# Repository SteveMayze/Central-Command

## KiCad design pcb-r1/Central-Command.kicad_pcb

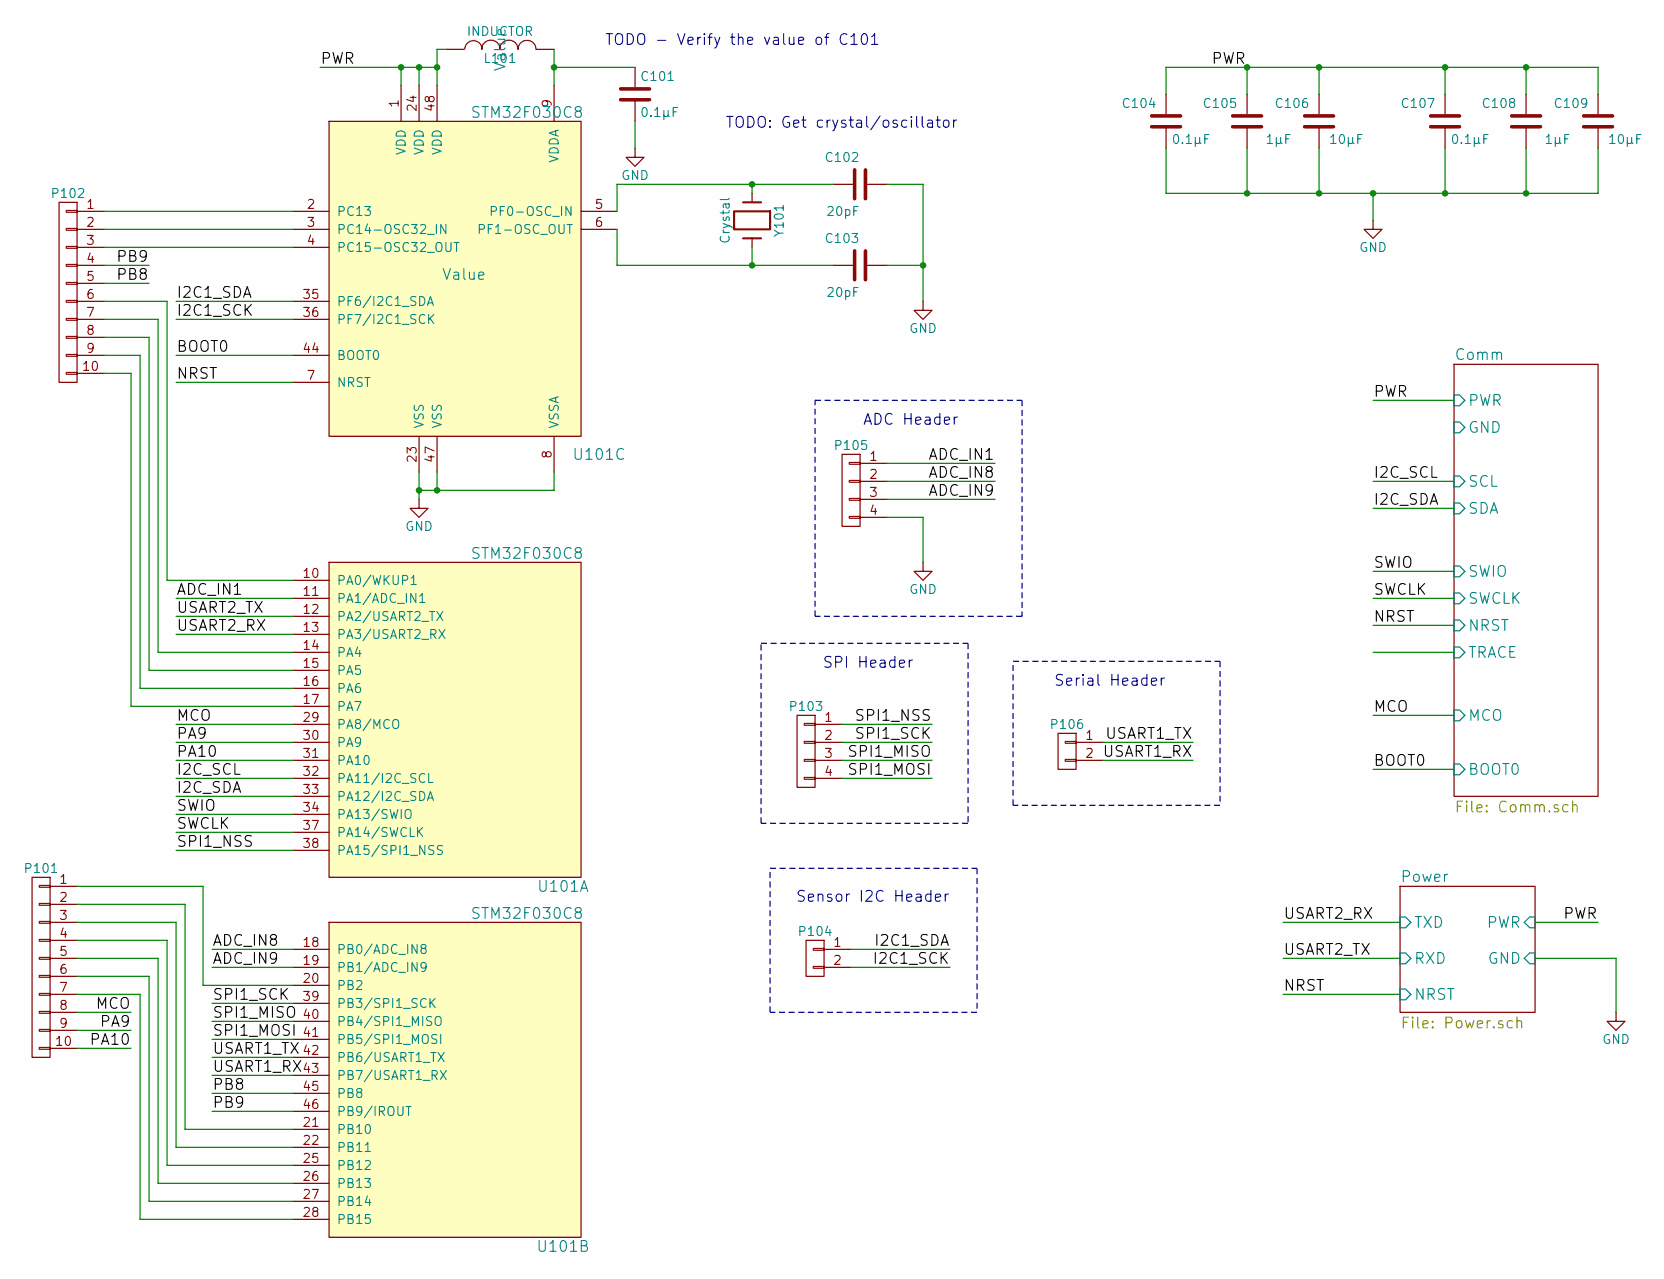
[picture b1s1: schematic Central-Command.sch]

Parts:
C101, C104, C107: 0.1μF; C_0805; DigiKeyPN 478-1395-1-ND
C102, C103: 20pF; C_0805; DigiKeyPN 1276-1829-1-ND
C105, C108: 1μF; C_1206; DigiKeyPN 311-1951-1-ND
C106, C109: 10μF; C_1206; DigiKeyPN 1276-2865-1-ND
L101: INDUCTOR; Neosid_Inductor_SM1206; MPN LQH31CN100K03L; DigiKeyPN 490-6588-1-ND
P101, P102: CONN_01X10; Pin_Header_Straight_1x10
P103, P105: CONN_01X04; Pin_Header_Straight_1x04
P104, P106: CONN_01X02; Pin_Header_Straight_1x02
U101: STM32F030C8; LQFP-48_7x7mm_Pitch0.5mm
Y101: Crystal; Crystal_HC49-U_Vertical; MPN FOXSLF/080-20; DigiKeyPN 631-1100-ND

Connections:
/ADC_IN1: P105.1, U101.11 (PA1/ADC_IN1)
/ADC_IN8: P105.2, U101.18 (PB0/ADC_IN8)
/ADC_IN9: P105.3, U101.19 (PB1/ADC_IN9)
/Comm/BOOT0: U101.44 (BOOT0); also elsewhere on the board
/Comm/NRST: U101.7 (NRST); also elsewhere on the board
/Comm/PWR: C104.2, C105.2, C106.2, C107.2, C108.2, C109.2, L101.1, U101.1 (VDD), U101.24 (VDD), U101.48 (VDD); also elsewhere on the board
/Comm/SCL: U101.32 (PA11/I2C_SCL); also elsewhere on the board
/Comm/SDA: U101.33 (PA12/I2C_SDA); also elsewhere on the board
/Comm/SWCLK: U101.37 (PA14/SWCLK); also elsewhere on the board
/Comm/SWIO: U101.34 (PA13/SWIO); also elsewhere on the board
/I2C1_SCK: P104.2, U101.36 (PF7/I2C1_SCK)
/I2C1_SDA: P104.1, U101.35 (PF6/I2C1_SDA)
/MCO: P101.8, U101.29 (PA8/MCO)
/PA9: P101.9, U101.30 (PA9)
/PA10: P101.10, U101.31 (PA10)
/PB8: P102.5, U101.45 (PB8)
/PB9: P102.4, U101.46 (PB9/IROUT)
/Power/RXD: U101.12 (PA2/USART2_TX); also elsewhere on the board
/Power/TXD: U101.13 (PA3/USART2_RX); also elsewhere on the board
/SPI1_MISO: P103.3, U101.40 (PB4/SPI1_MISO)
/SPI1_MOSI: P103.4, U101.41 (PB5/SPI1_MOSI)
/SPI1_NSS: P103.1, U101.38 (PA15/SPI1_NSS)
/SPI1_SCK: P103.2, U101.39 (PB3/SPI1_SCK)
/USART1_RX: P106.2, U101.43 (PB7/USART1_RX)
/USART1_TX: P106.1, U101.42 (PB6/USART1_TX)
GND: C101.2, C102.2, C103.2, C104.1, C105.1, C106.1, C107.1, C108.1, C109.1, P105.4, U101.8 (VSSA), U101.23 (VSS), U101.47 (VSS); also elsewhere on the board
unnamed: C101.1, L101.2, U101.9 (VDDA)
unnamed: C102.1, U101.5 (PF0-OSC_IN), Y101.1
unnamed: C103.1, U101.6 (PF1-OSC_OUT), Y101.2
unnamed: P101.1, U101.20 (PB2)
unnamed: P101.2, U101.21 (PB10)
unnamed: P101.3, U101.22 (PB11)
unnamed: P101.4, U101.25 (PB12)
unnamed: P101.5, U101.26 (PB13)
unnamed: P101.6, U101.27 (PB14)
unnamed: P101.7, U101.28 (PB15)
unnamed: P102.1, U101.2 (PC13)
unnamed: P102.2, U101.3 (PC14-OSC32_IN)
unnamed: P102.3, U101.4 (PC15-OSC32_OUT)
unnamed: P102.6, U101.10 (PA0/WKUP1)
unnamed: P102.7, U101.14 (PA4)
unnamed: P102.8, U101.15 (PA5)
unnamed: P102.9, U101.16 (PA6)
unnamed: P102.10, U101.17 (PA7)

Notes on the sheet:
TODO: Get crystal/oscillator
ADC Header
SPI Header
Serial Header
Sensor I2C Header
TODO - Verify the value of C101

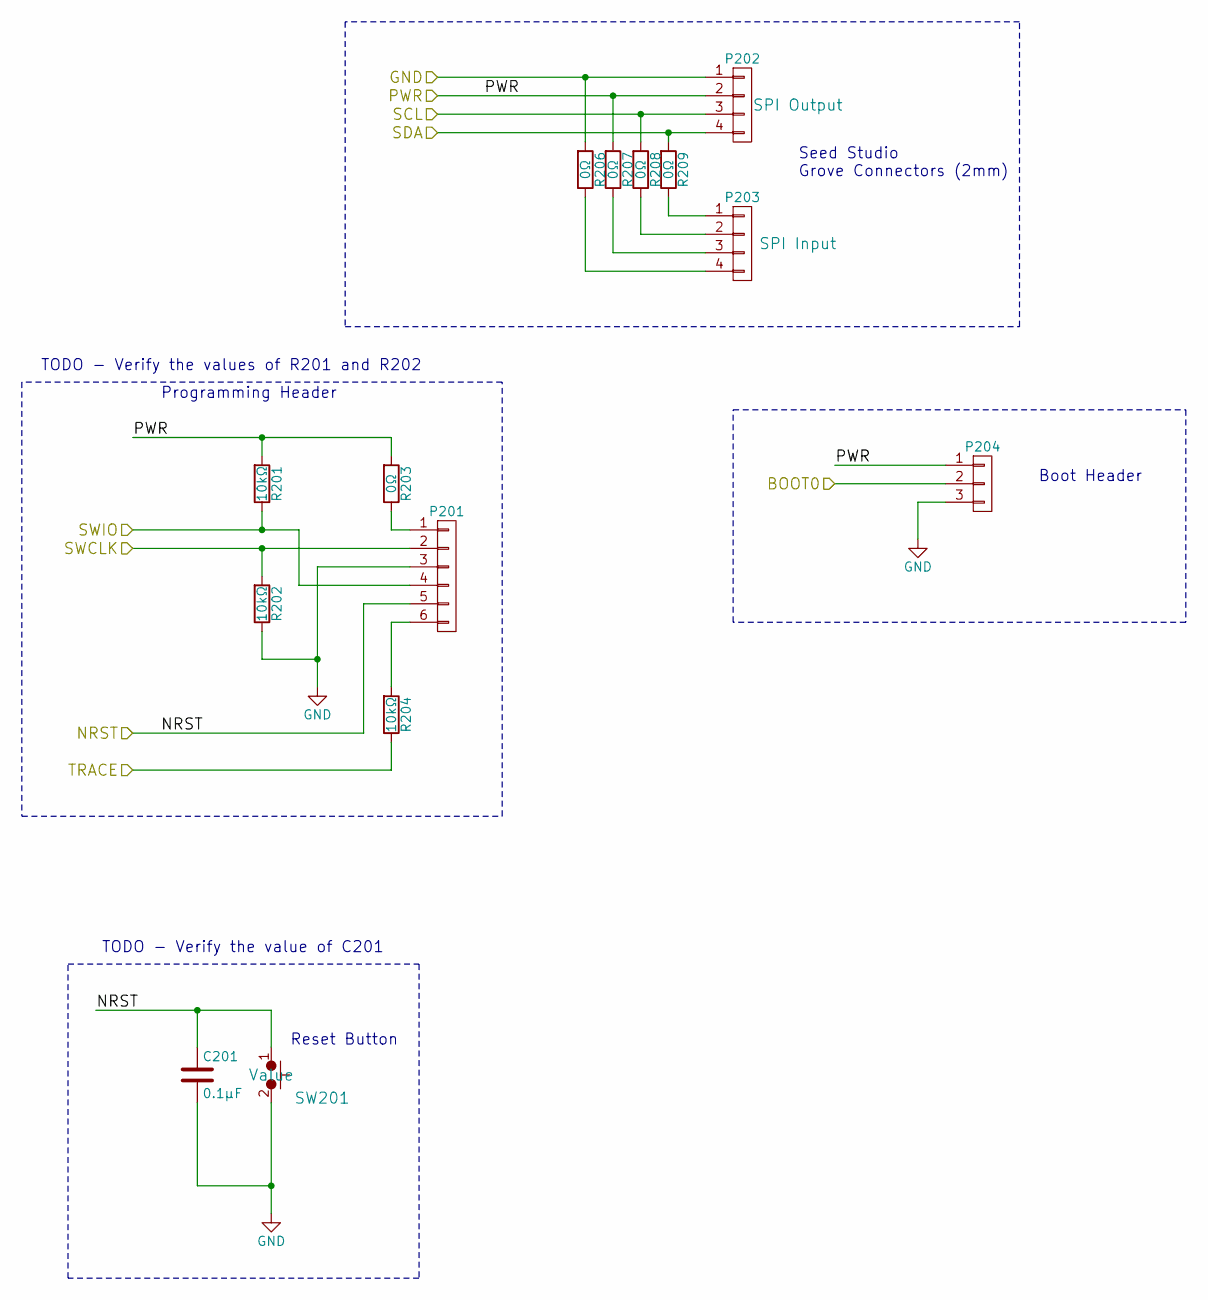
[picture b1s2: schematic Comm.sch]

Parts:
C201: 0.1μF; C_0805; DigiKeyPN 478-1395-1-ND
P201: CONN_01X06; Pin_Header_Straight_1x06; DigiKeyPN 952-2247-ND
P202, P203: CONN_01X04; Grove-2mm; MPN Value
P204: CONN_01X03; Pin_Header_Straight_1x03
R201, R202, R204: 10kΩ; R_0805; DigiKeyPN 311-10.0KCRCT-ND
R203, R206, R207, R208, R209: 0Ω; R_0805
SW201: TL3315NF160Q; PTS525SM15SMTR2LFS; MPN FSM2JSMAA; DigiKeyPN FSM2JSMAA-ND

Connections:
/Comm/BOOT0: P204.2; also elsewhere on the board
/Comm/NRST: C201.1, P201.5, SW201.1; also elsewhere on the board
/Comm/PWR: P202.2, P204.1, R201.2, R203.2, R207.2; also elsewhere on the board
/Comm/SCL: P202.3, R208.2; also elsewhere on the board
/Comm/SDA: P202.4, R209.2; also elsewhere on the board
/Comm/SWCLK: P201.2, R202.2; also elsewhere on the board
/Comm/SWIO: P201.4, R201.1; also elsewhere on the board
/Comm/TRACE: R204.1
GND: C201.2, P201.3, P202.1, P204.3, R202.1, R206.2, SW201.2; also elsewhere on the board
unnamed: P201.1, R203.1
unnamed: P201.6, R204.2
unnamed: P203.1, R209.1
unnamed: P203.2, R208.1
unnamed: P203.3, R207.1
unnamed: P203.4, R206.1

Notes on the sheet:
Reset Button
Programming Header
Seed Studio Grove Connectors (2mm)
Boot Header
TODO - Verify the values of R201 and R202
TODO - Verify the value of C201

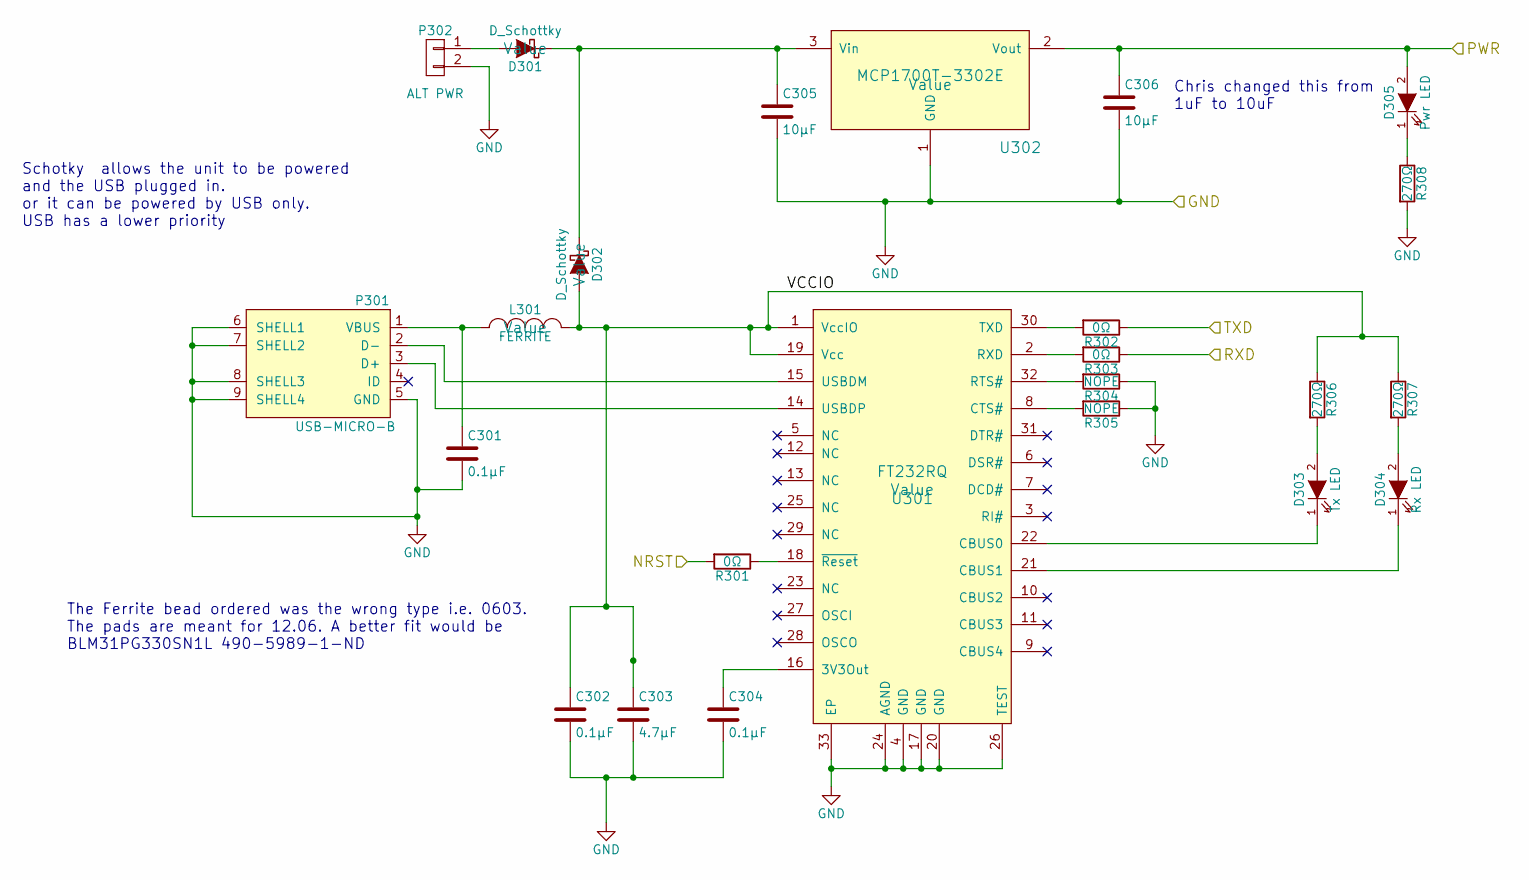
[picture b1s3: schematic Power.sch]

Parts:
C301: 0.1μF; C_0805
C302, C304: 0.1μF; C_0805; DigiKeyPN 478-1395-1-ND
C303: 4.7μF; C_0805; DigiKeyPN 1276-1856-1-ND
C305: 10μF; C_1210; DigiKeyPN 1276-2865-1-ND
C306: 10μF; C_1210
D301, D302: D_Schottky; SMA_Standard; MPN B130-13-F; DigiKeyPN B130-FDICT-ND
D303: Tx LED; LED-0805
D304: Rx LED; LED-0805
D305: Pwr LED; LED-0805; Voltage Value; DigiKeyPN Value
L301: FERRITE; Neosid_Inductor_SM1206; Voltage Value; MPN BLM31PG330SN1L; DigiKeyPN 490-5989-1-ND
P301: USB-MICRO-B; USB_Micro_B
P302: ALT PWR; Pin_Header_Straight_1x02
R301, R302, R303: 0Ω; R_0805
R304, R305: NOPE; R_0805
R306, R307, R308: 270Ω; R_0805
U301: FT232RQ; QFN-32-1EP_5x5mm_Pitch0.5mm; MPN FT232RQ-REEL; DigiKeyPN 768-1008-1-ND
U302: MCP1700T-3302E; SOT-23; MPN MCP1700T-3302E/TT; DigiKeyPN MCP1700T3302ETTCT-ND

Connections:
/Comm/NRST: R301.2; also elsewhere on the board
/Comm/PWR: C306.1, D305.2 (A), U302.2 (Vout); also elsewhere on the board
/Power/RXD: R303.1; also elsewhere on the board
/Power/TXD: R302.1; also elsewhere on the board
/Power/VCCIO: C302.1, C303.1, D302.2 (A), L301.2, R306.1, R307.1, U301.1 (VccIO), U301.19 (Vcc)
GND: C301.2, C302.2, C303.2, C304.2, C305.2, C306.2, P301.5 (GND), P301.6 (SHELL1), P301.7 (SHELL2), P301.8 (SHELL3), P301.9 (SHELL4), P302.2, R304.1, R305.1, R308.2, U301.4 (GND), U301.17 (GND), U301.20 (GND), U301.24 (AGND), U301.26 (TEST), U301.33 (EP), U302.1 (GND); also elsewhere on the board
unnamed: C301.1, L301.1, P301.1 (VBUS)
unnamed: C304.1, U301.16 (3V3Out)
unnamed: C305.1, D301.1 (K), D302.1 (K), U302.3 (Vin)
unnamed: D301.2 (A), P302.1
unnamed: D303.1 (K), U301.22 (CBUS0)
unnamed: D303.2 (A), R306.2
unnamed: D304.1 (K), U301.21 (CBUS1)
unnamed: D304.2 (A), R307.2
unnamed: D305.1 (K), R308.1
unnamed: P301.2 (D-), U301.15 (USBDM)
unnamed: P301.3 (D+), U301.14 (USBDP)
unnamed: R301.1, U301.18 (~Reset)
unnamed: R302.2, U301.30 (TXD)
unnamed: R303.2, U301.2 (RXD)
unnamed: R304.2, U301.32 (RTS#)
unnamed: R305.2, U301.8 (CTS#)

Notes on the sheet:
Schotky allows the unit to be powered and the USB plugged in. or it can be powered by USB only. USB has a lower priority
Chris changed this from 1uF to 10uF
The Ferrite bead ordered was the wrong type i.e. 0603. The pads are meant for 12.06. A better fit would be BLM31PG330SN1L 490-5989-1-ND

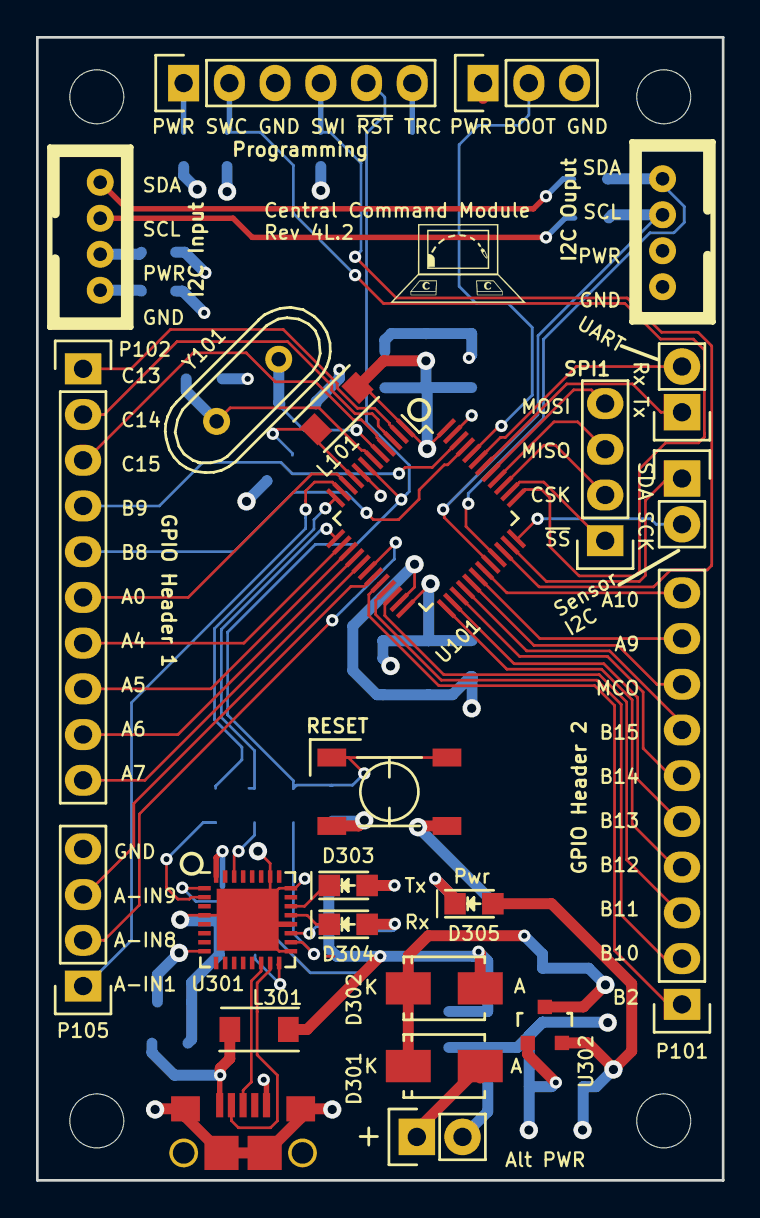
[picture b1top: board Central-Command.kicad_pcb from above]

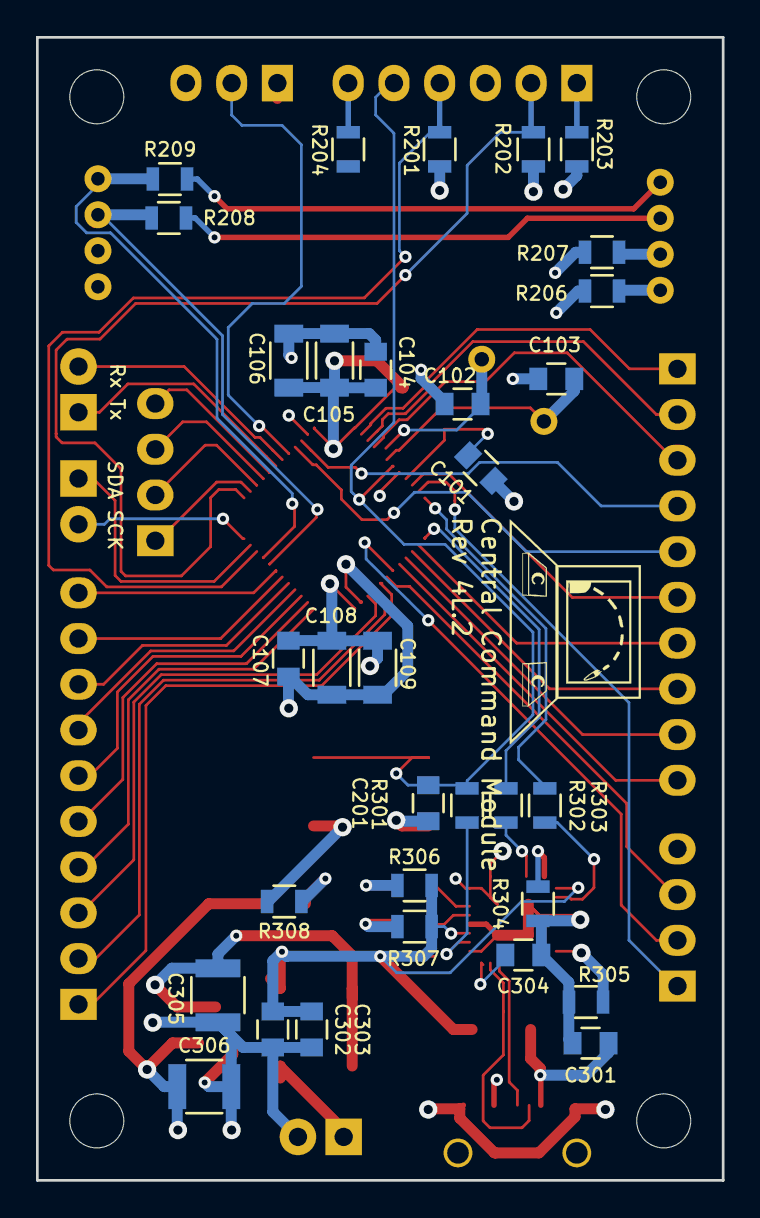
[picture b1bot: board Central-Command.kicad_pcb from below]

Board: 4 copper layers, 38.1 x 63.5 mm, 56 parts (32 on the bottom side), 67 nets.

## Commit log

2015-10-12 Added kicad project
2015-10-12 Initial place holder for the micro symbol
2015-10-13 Completed the symbol for the micro
2015-11-02 Updated the Micro symbol as per datasheet markup and started adding some more symols as per CC07-CC11
2015-11-06 Added linear voltage regulator
2015-11-22 Started layout to figure out sizes and features
2015-11-24 Updated for CC13 and CC14
2015-11-27 Added power block hierarchical sheet, FT232RQ and Micro-B USB symbols
2015-11-29 Added further enhancements to the power block
2015-12-08 Updated the schematic with the latest from CC17
2015-12-08 Edited the Central-Command.sch and forced the order of the hierarchical sheets to match the reference schematic annotations. Also annotated
2015-12-08 Added the Grove2mm connector footprint
2015-12-08 Started the part to footprint association
2015-12-09 Removed the *-cache.lib from the .gitignore. This causes clashes with other clones
2015-12-09 Started preliminary layout of the parts
2015-12-10 New initial layout
2015-12-12 Corrected the symbol and footprint for the reset switch
2015-12-25 Updates to the PCB
2015-12-26 Intermediate save of the layout
2015-12-26 Started the basic layout.
2015-12-27 Final draft layout. Published to build log as V01
2015-12-28 Completed the layout. Saving before sending off to Fab.
2015-12-31 Realigned the UART and Sensor labels
2016-01-04 Generated the final Gerbers for fabrication
2016-01-10 Preparing the BOM
2016-01-10 Added the MPN for the crystal
2016-02-02 Updated the parts for the BOM
2016-02-02 Updated the parts with further DigiKeyPN
2016-02-13 Made the correction to the Tx Rx on the schematic and added a comment regarding the Ferrite Bead
2016-02-13 Corrected the routing of the Tx and Rx
2016-05-07 Updated the L301 to a 1206 part rather than 0603
2016-06-20 Central Command update
2016-07-05 Completed revised board 4L.2 and submitted to OSH Park
